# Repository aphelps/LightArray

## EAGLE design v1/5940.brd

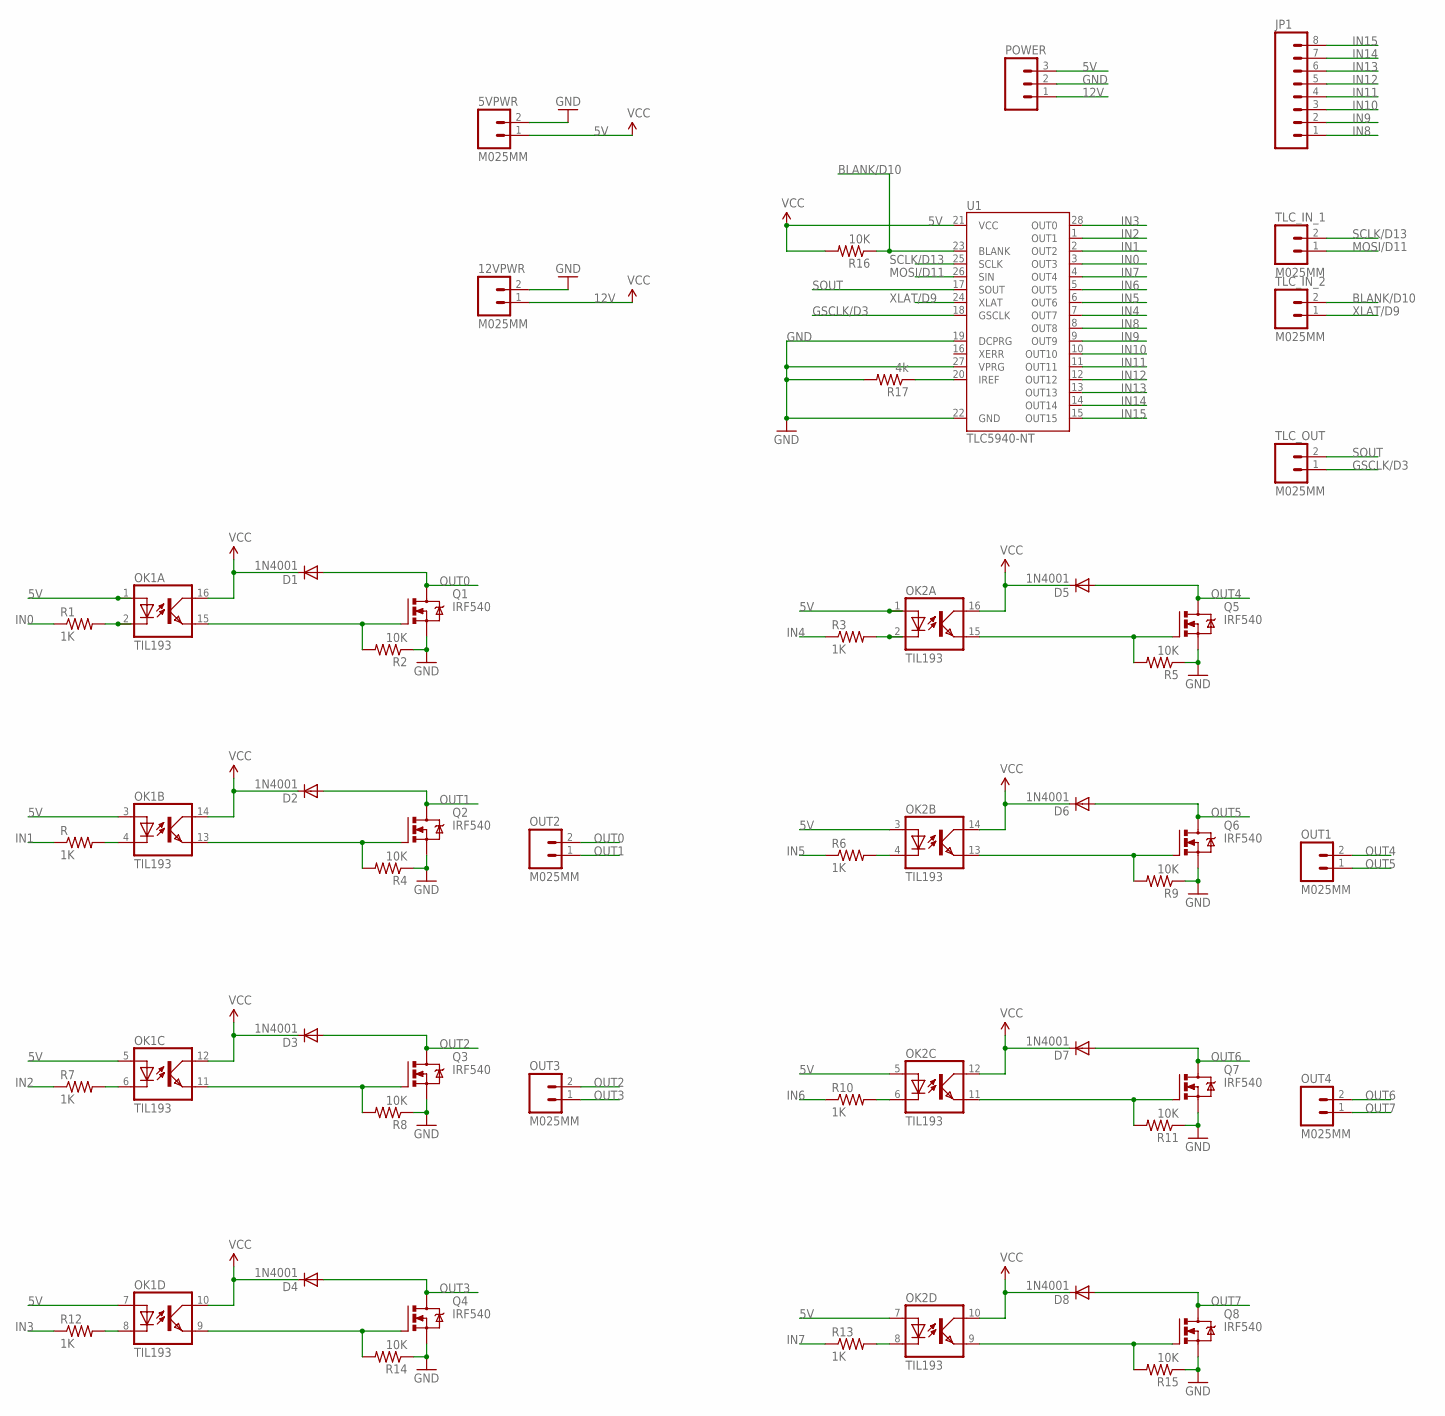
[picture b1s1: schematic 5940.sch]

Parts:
5VPWR, 12VPWR: M025MM; SCREWTERMINAL-5MM-2
D1, D2, D3, D4, D5, D6, D7, D8: 1N4001; DIODE-1N4001
JP1: M08; 1X08_ROUND
OK1, OK2: TIL193; DIL16
OUT1, OUT2, OUT3, OUT4: M025MM; SCREWTERMINAL-5MM-2
POWER: M03LONGPADS; 1X03_LONGPADS
Q1, Q2, Q3, Q4, Q5, Q6, Q7, Q8: IRF540; TO220BV
R, R1, R3, R6, R7, R10, R12, R13: 1K; AXIAL-0.4
R2, R4, R5, R8, R9, R11, R14, R15, R16: 10K; AXIAL-0.4
R17: 4k; AXIAL-0.4
TLC_IN_1, TLC_IN_2: M025MM; SCREWTERMINAL-5MM-2
TLC_OUT: M025MM; SCREWTERMINAL-5MM-2
U1: TLC5940-NT; DIL28-3

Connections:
5V: 5VPWR.1, OK1.1 (A), OK1.3 (A), OK1.5 (A), OK1.7 (A), OK2.1 (A), OK2.3 (A), OK2.5 (A), OK2.7 (A), POWER.3, R16.P$2 (2), U1.21 (VCC)
12V: 12VPWR.1, D1.C, D2.C, D3.C, D4.C, D5.C, D6.C, D7.C, D8.C, OK1.10 (COL), OK1.12 (COL), OK1.14 (COL), OK1.16 (COL), OK2.10 (COL), OK2.12 (COL), OK2.14 (COL), OK2.16 (COL), POWER.1
BLANK/D10: R16.P$1 (1), TLC_IN_2.2, U1.23 (BLANK)
GND: 5VPWR.2, 12VPWR.2, POWER.2, Q1.S, Q2.S, Q3.S, Q4.S, Q5.S, Q6.S, Q7.S, Q8.S, R2.P$1 (1), R4.P$1 (1), R5.P$1 (1), R8.P$1 (1), R9.P$1 (1), R11.P$1 (1), R14.P$1 (1), R15.P$1 (1), R17.P$2 (2), U1.19 (DCPRG), U1.22 (GND), U1.27 (VPRG)
GSCLK/D3: TLC_OUT.1, U1.18 (GSCLK)
IN0: R1.P$1 (1), U1.3 (OUT3)
IN1: R.P$1 (1), U1.2 (OUT2)
IN2: R7.P$1 (1), U1.1 (OUT1)
IN3: R12.P$1 (1), U1.28 (OUT0)
IN4: R3.P$1 (1), U1.7 (OUT7)
IN5: R6.P$1 (1), U1.6 (OUT6)
IN6: R10.P$1 (1), U1.5 (OUT5)
IN7: R13.P$1 (1), U1.4 (OUT4)
IN8: JP1.1, U1.8 (OUT8)
IN9: JP1.2, U1.9 (OUT9)
IN10: JP1.3, U1.10 (OUT10)
IN11: JP1.4, U1.11 (OUT11)
IN12: JP1.5, U1.12 (OUT12)
IN13: JP1.6, U1.13 (OUT13)
IN14: JP1.7, U1.14 (OUT14)
IN15: JP1.8, U1.15 (OUT15)
MOSI/D11: TLC_IN_1.1, U1.26 (SIN)
unnamed: OK2.2 (C), R3.P$2 (2)
unnamed: OK1.4 (C), R.P$2 (2)
unnamed: OK2.15 (EMIT), Q5.G, R5.P$2 (2)
unnamed: OK1.15 (EMIT), Q1.G, R2.P$2 (2)
unnamed: OK1.13 (EMIT), Q2.G, R4.P$2 (2)
unnamed: OK1.2 (C), R1.P$2 (2)
unnamed: OK2.13 (EMIT), Q6.G, R9.P$2 (2)
unnamed: OK2.4 (C), R6.P$2 (2)
unnamed: OK1.11 (EMIT), Q3.G, R8.P$2 (2)
unnamed: OK2.11 (EMIT), Q7.G, R11.P$2 (2)
unnamed: OK1.6 (C), R7.P$2 (2)
unnamed: OK2.6 (C), R10.P$2 (2)
unnamed: OK1.9 (EMIT), Q4.G, R14.P$2 (2)
unnamed: OK2.9 (EMIT), Q8.G, R15.P$2 (2)
unnamed: OK1.8 (C), R12.P$2 (2)
unnamed: OK2.8 (C), R13.P$2 (2)
unnamed: R17.P$1 (1), U1.20 (IREF)
OUT0: D1.A, OUT2.2, Q1.D
OUT1: D2.A, OUT2.1, Q2.D
OUT2: D3.A, OUT3.2, Q3.D
OUT3: D4.A, OUT3.1, Q4.D
OUT4: D5.A, OUT1.2, Q5.D
OUT5: D6.A, OUT1.1, Q6.D
OUT6: D7.A, OUT4.2, Q7.D
OUT7: D8.A, OUT4.1, Q8.D
SCLK/D13: TLC_IN_1.2, U1.25 (SCLK)
SOUT: TLC_OUT.2, U1.17 (SOUT)
XLAT/D9: TLC_IN_2.1, U1.24 (XLAT)

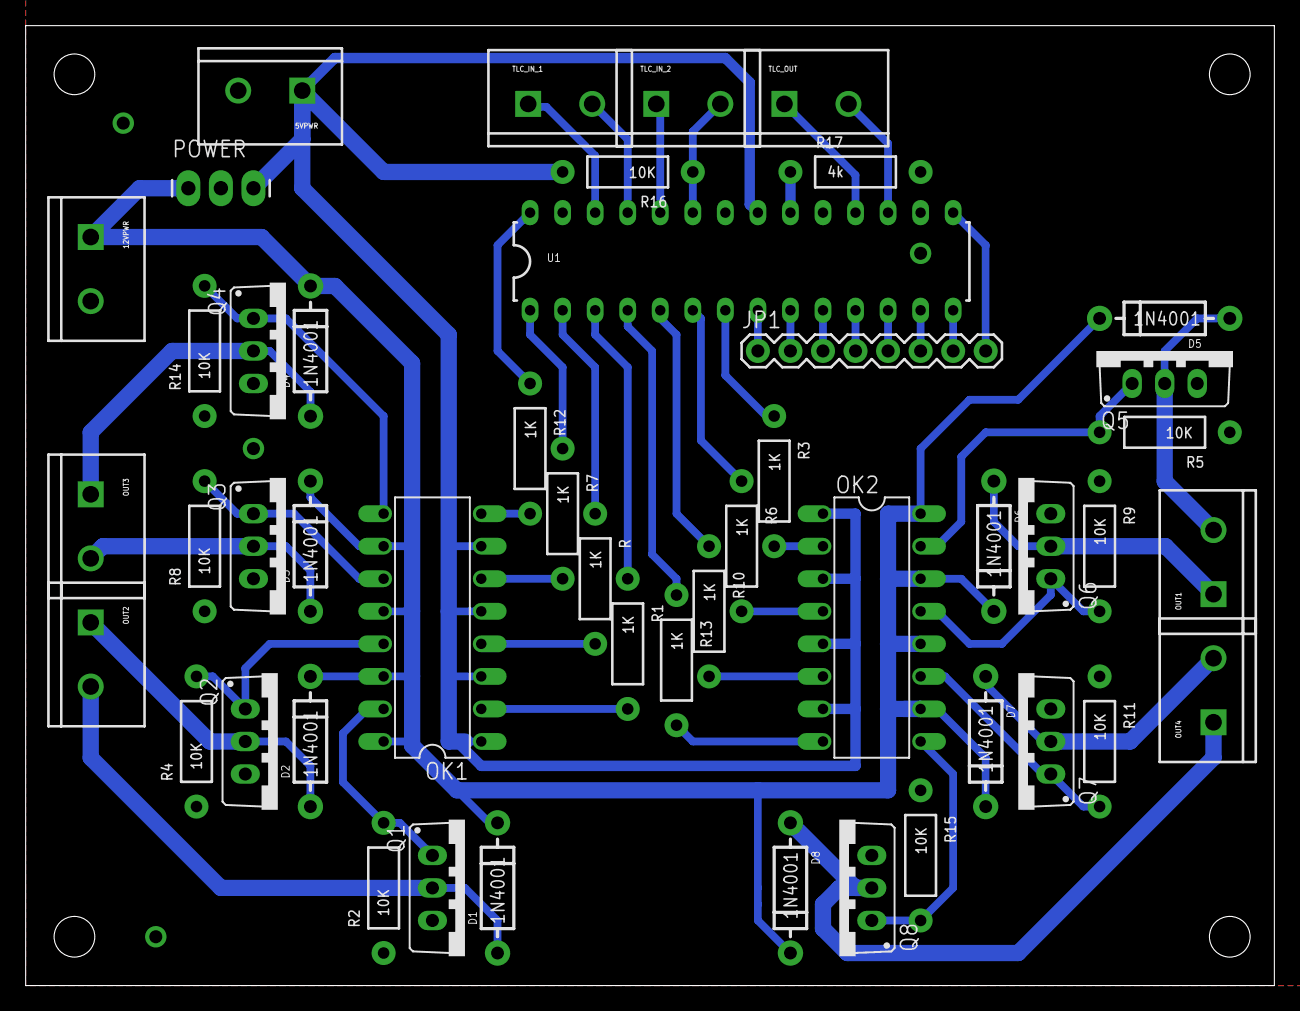
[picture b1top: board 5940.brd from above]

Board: 2 copper layers, 97.5 x 74.9 mm, 48 parts (0 on the bottom side), 50 nets.

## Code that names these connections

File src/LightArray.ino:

/*
    Basic Pin setup:
    ------------                                  ---u----
    ARDUINO   13|-> SCLK (pin 25)           OUT1 |1     28| OUT channel 0
              12|                           OUT2 |2     27|-> GND (VPRG)
              11|-> SIN (pin 26)            OUT3 |3     26|-> SIN (pin 11)
              10|-> BLANK (pin 23)          OUT4 |4     25|-> SCLK (pin 13)
               9|-> XLAT (pin 24)             .  |5     24|-> XLAT (pin 9)
               8|                             .  |6     23|-> BLANK (pin 10)
               7|                             .  |7     22|-> GND
               6|                             .  |8     21|-> VCC (+5V)
               5|                             .  |9     20|-> 2K Resistor -> GND
               4|                             .  |10    19|-> +5V (DCPRG)
               3|-> GSCLK (pin 18)            .  |11    18|-> GSCLK (pin 3)
               2|                             .  |12    17|-> SOUT
               1|                             .  |13    16|-> XERR
               0|                           OUT14|14    15| OUT channel 15
    ------------                                  --------

    -  Put the longer leg (anode) of the LEDs in the +5V and the shorter leg
         (cathode) in OUT(0-15).
    -  +5V from Arduino -> TLC pin 21 and 19     (VCC and DCPRG)
    -  GND from Arduino -> TLC pin 22 and 27     (GND and VPRG)
    -  digital 3        -> TLC pin 18            (GSCLK)
    -  digital 9        -> TLC pin 24            (XLAT)
    -  digital 10       -> TLC pin 23            (BLANK)
    -  digital 11       -> TLC pin 26            (SIN)
    -  digital 13       -> TLC pin 25            (SCLK)
    -  The 2K resistor between TLC pin 20 and GND will let ~20mA through each
       LED.  To be precise, it's I = 39.06 / R (in ohms).  This doesn't depend
       on the LED driving voltage.
    - (Optional): put a pull-up resistor (~10k) between +5V and BLANK so that
                  all the LEDs will turn off when the Arduino is reset.

    If you are daisy-chaining more than one TLC, connect the SOUT of the first
    TLC to the SIN of the next.  All the other pins should just be connected
    together:
        BLANK on Arduino -> BLANK of TLC1 -> BLANK of TLC2 -> ...
        XLAT on Arduino  -> XLAT of TLC1  -> XLAT of TLC2  -> ...
    The one exception is that each TLC needs it's own resistor between pin 20
    and GND.

    This library uses the PWM output ability of digital pins 3, 9, 10, and 11.
    Do not use analogWrite(...) on these pins.

    This sketch does the Knight Rider strobe across a line of LEDs.

    Alex Leone <acleone ~AT~ gmail.com>, 2009-02-03 */

#include "Tlc5940.h"

void setup()
{
  /* Call Tlc.init() to setup the tlc.
     You can optionally pass an initial PWM value (0 - 4095) for all channels.*/
  Tlc.init();
}

/* This loop will create a Knight Rider-like effect if you have LEDs plugged
   into all the TLC outputs.  NUM_TLCS is defined in "tlc_config.h" in the
   library folder.  After editing tlc_config.h for your setup, delete the
   Tlc5940.o file to save the changes. */

void loop()
{
  int direction = 1;
  for (int channel = 0; channel < NUM_TLCS * 16; channel += direction) {

    /* Tlc.clear() sets all the grayscale values to zero, but does not send
       them to the TLCs.  To actually send the data, call Tlc.update() */
    Tlc.clear();

    /* Tlc.set(channel (0-15), value (0-4095)) sets the grayscale value for
       one channel (15 is OUT15 on the first TLC, if multiple TLCs are daisy-
       chained, then channel = 16 would be OUT0 of the second TLC, etc.).

       value goes from off (0) to always on (4095).

       Like Tlc.clear(), this function only sets up the data, Tlc.update()
       will send the data. */
    if (channel == 0) {
      direction = 1;
    } else {
      Tlc.set(channel - 1, 1000);
    }
    Tlc.set(channel, 4095);
    if (channel != NUM_TLCS * 16 - 1) {
      Tlc.set(channel + 1, 1000);
    } else {
      direction = -1;
    }

    /* Tlc.update() sends the data to the TLCs.  This is when the LEDs will
       actually change. */
    Tlc.update();

    delay(75);
  }

}

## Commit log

2016-08-17 Initial commit of Othermill TLC5940 controller
2016-08-20 Minor updates
2016-08-23 Added initial arduino code and platformio build config

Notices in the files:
parts and their libraries:
SparkFun-DiscreteSemi: Licensing: Creative Commons ShareAlike 4.0 International - https://creativecommons.org/licenses/by-sa/4.0
